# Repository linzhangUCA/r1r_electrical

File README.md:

# homer_ee
Electrical and electronics design for HomeR

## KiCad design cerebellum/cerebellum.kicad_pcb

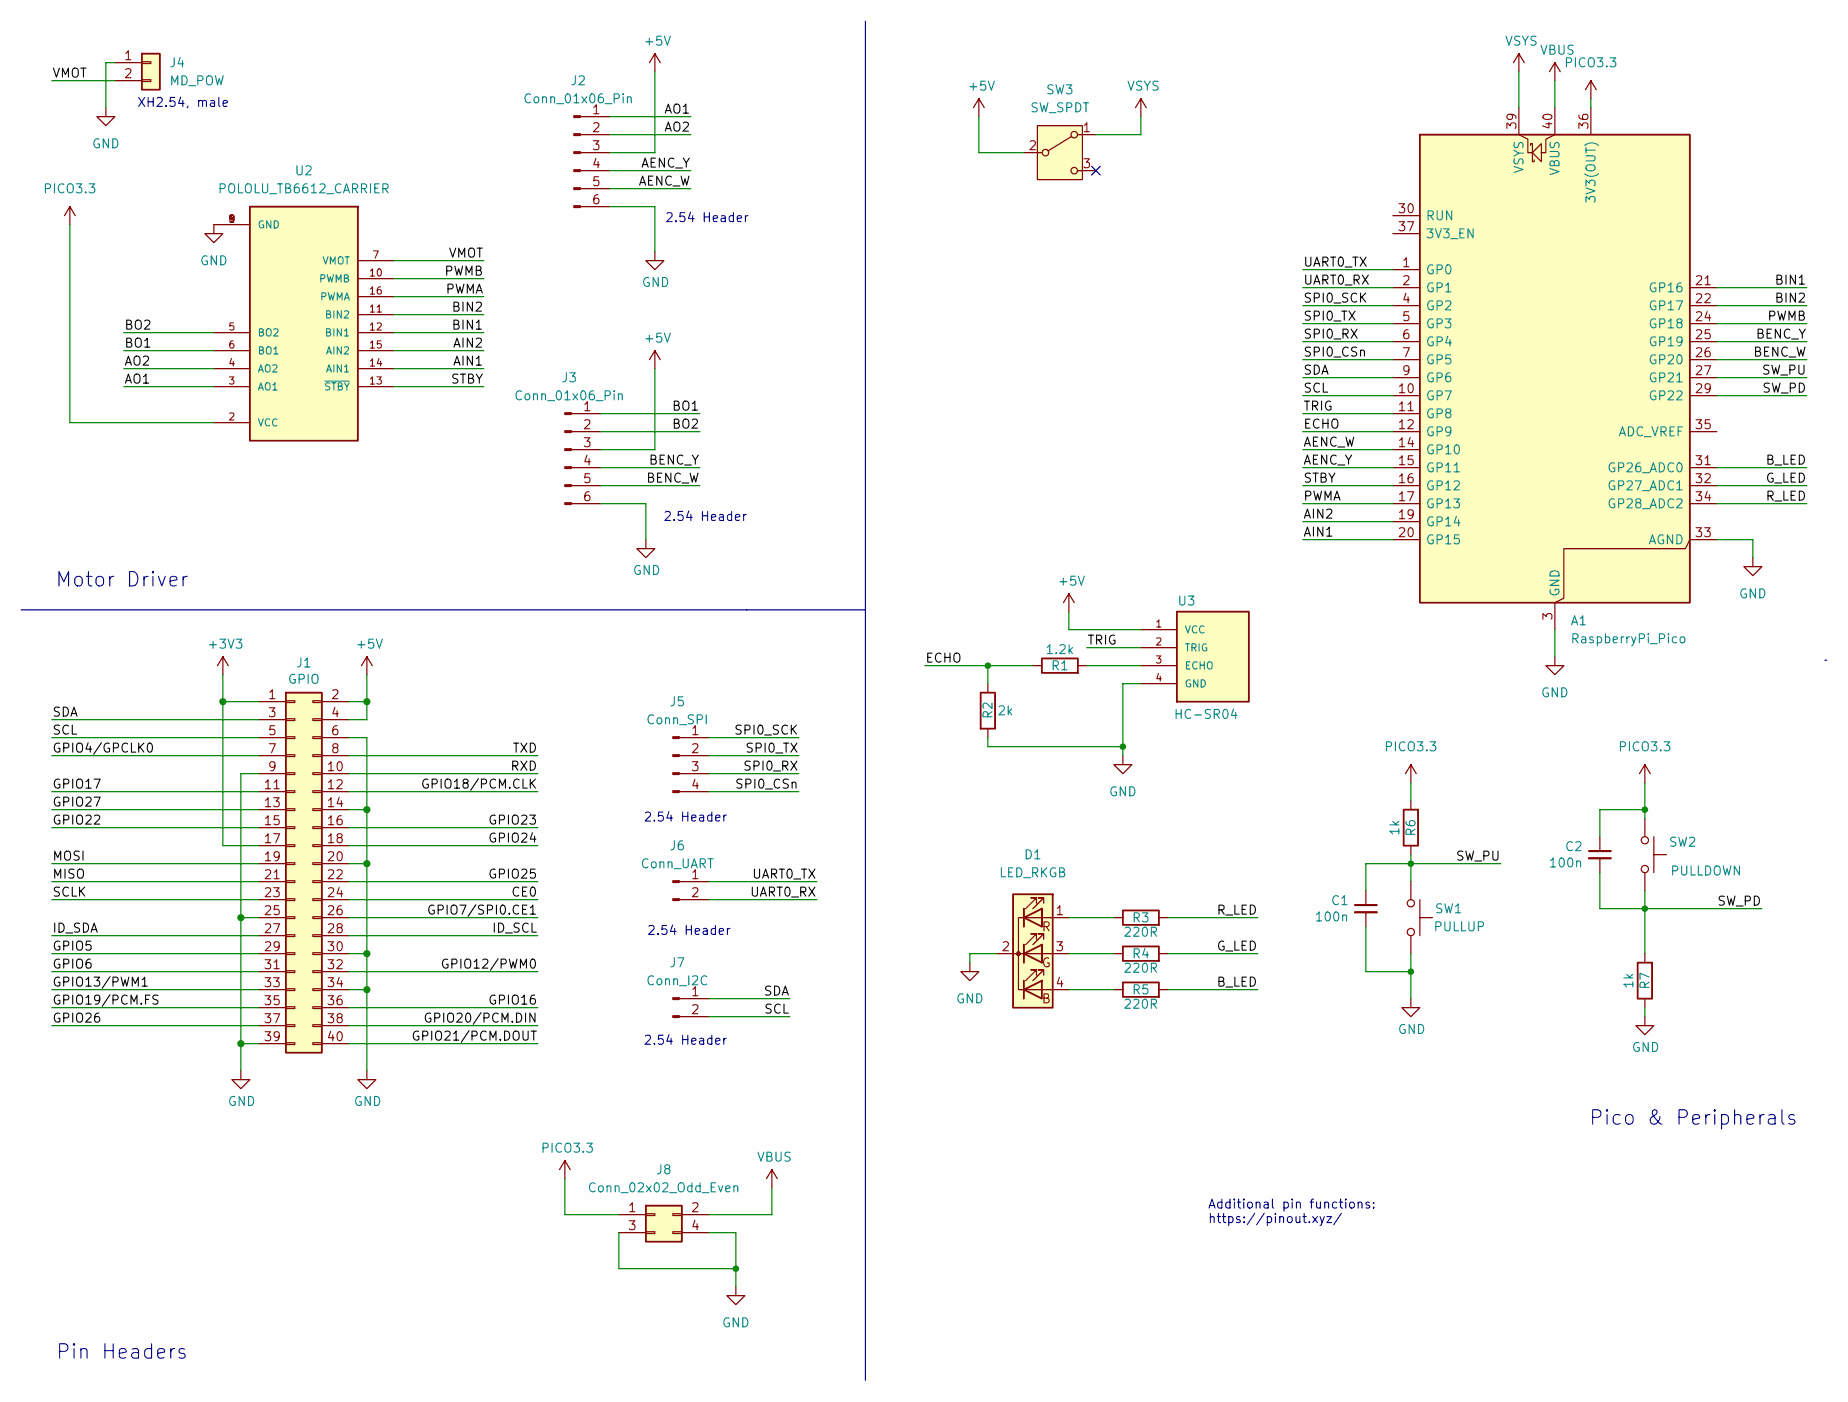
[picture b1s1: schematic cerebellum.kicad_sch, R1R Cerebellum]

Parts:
A1: RaspberryPi_Pico; RaspberryPi_Pico_Common_THT
C1, C2: 100n; C_Disc_D4.7mm_W2.5mm_P5.00mm
D1: LED_RKGB; LED_D5.0mm-4_RGB_Wide_Pins
J1: GPIO; PinSocket_2x20_P2.54mm_Vertical
J2, J3: Conn_01x06_Pin; PinHeader_1x06_P2.54mm_Vertical
J4: MD_POW; PinHeader_1x02_P2.54mm_Horizontal
J5: Conn_SPI; PinHeader_1x04_P2.54mm_Vertical
J6: Conn_UART; PinHeader_1x02_P2.54mm_Vertical
J7: Conn_I2C; PinHeader_1x02_P2.54mm_Vertical
J8: Conn_02x02_Odd_Even; PinHeader_2x02_P2.54mm_Vertical
R1: 1.2k; R_Axial_DIN0207_L6.3mm_D2.5mm_P10.16mm_Horizontal
R2: 2k; R_Axial_DIN0207_L6.3mm_D2.5mm_P10.16mm_Horizontal
R3, R4, R5: 220R; R_Axial_DIN0207_L6.3mm_D2.5mm_P10.16mm_Horizontal
R6, R7: 1k; R_Axial_DIN0207_L6.3mm_D2.5mm_P10.16mm_Horizontal
SW1: PULLUP; SW_PUSH_6mm_H5mm
SW2: PULLDOWN; SW_PUSH_6mm_H5mm
SW3: SW_SPDT; PinHeader_1x03_P2.54mm_Vertical
U2: POLOLU_TB6612_CARRIER; POLOLU_TB6612
U3: HC-SR04; XCVR_HC-SR04

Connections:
+3V3: J1.1, J1.17
+5V: J1.2, J1.4, J2.3, J3.3, SW3.2 (B), U3.1 (VCC)
/AENC_W: A1.14 (GP10), J2.5
/AENC_Y: A1.15 (GP11), J2.4
/AIN1: A1.20 (GP15), U2.14 (AIN1)
/AIN2: A1.19 (GP14), U2.15 (AIN2)
/AO1: J2.1, U2.3 (AO1)
/AO2: J2.2, U2.4 (AO2)
/BENC_W: A1.26 (GP20), J3.5
/BENC_Y: A1.25 (GP19), J3.4
/BIN1: A1.21 (GP16), U2.12 (BIN1)
/BIN2: A1.22 (GP17), U2.11 (BIN2)
/BO1: J3.1, U2.6 (BO1)
/BO2: J3.2, U2.5 (BO2)
/B_LED: A1.31 (GP26_ADC0), R5.2
/CE0: J1.24
/ECHO: A1.12 (GP9), R1.1, R2.1
/GPIO4/GPCLK0: J1.7
/GPIO5: J1.29
/GPIO6: J1.31
/GPIO7/SPI0.CE1: J1.26
/GPIO12/PWM0: J1.32
/GPIO13/PWM1: J1.33
/GPIO16: J1.36
/GPIO17: J1.11
/GPIO18/PCM.CLK: J1.12
/GPIO19/PCM.FS: J1.35
/GPIO20/PCM.DIN: J1.38
/GPIO21/PCM.DOUT: J1.40
/GPIO22: J1.15
/GPIO23: J1.16
/GPIO24: J1.18
/GPIO25: J1.22
/GPIO26: J1.37
/GPIO27: J1.13
/G_LED: A1.32 (GP27_ADC1), R4.2
/ID_SCL: J1.28
/ID_SDA: J1.27
/MISO: J1.21
/MOSI: J1.19
/PWMA: A1.17 (GP13), U2.16 (PWMA)
/PWMB: A1.24 (GP18), U2.10 (PWMB)
/RXD: J1.10
/R_LED: A1.34 (GP28_ADC2), R3.2
/SCL: A1.10 (GP7), J1.5, J7.2
/SCLK: J1.23
/SDA: A1.9 (GP6), J1.3, J7.1
/SPI0_CSn: A1.7 (GP5), J5.4
/SPI0_RX: A1.6 (GP4), J5.3
/SPI0_SCK: A1.4 (GP2), J5.1
/SPI0_TX: A1.5 (GP3), J5.2
/STBY: A1.16 (GP12), U2.13 (~STBY)
/SW_PD: A1.29 (GP22), C2.2, R7.2, SW2.2
/SW_PU: A1.27 (GP21), C1.1, R6.1, SW1.1
/TRIG: A1.11 (GP8), U3.2 (TRIG)
/TXD: J1.8
/UART0_RX: A1.2 (GP1), J6.2
/UART0_TX: A1.1 (GP0), J6.1
/VMOT: J4.2, U2.7 (VMOT)
GND: A1.3 (GND), A1.8 (GND), A1.13 (GND), A1.18 (GND), A1.23 (GND), A1.28 (GND), A1.33 (AGND), A1.38 (GND), C1.2, D1.2 (K), J1.6, J1.9, J1.14, J1.20, J1.25, J1.30, J1.34, J1.39, J2.6, J3.6, J4.1, J8.3, J8.4, R2.2, R7.1, SW1.2, U2.1 (GND), U2.8 (GND), U2.9 (GND), U3.4 (GND)
unnamed: D1.4 (BA), R5.1
unnamed: D1.3 (GA), R4.1
unnamed: D1.1 (RA), R3.1
unnamed: R1.2, U3.3 (ECHO)
PICO3.3: A1.36 (3V3(OUT)), C2.1, J8.1, R6.2, SW2.1, U2.2 (VCC)
VBUS: A1.40 (VBUS), J8.2
VSYS: A1.39 (VSYS), SW3.1 (A)

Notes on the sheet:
2.54 Header
Pin Headers
Additional pin functions: https://pinout.xyz/
Pico & Peripherals
Motor Driver
XH2.54, male

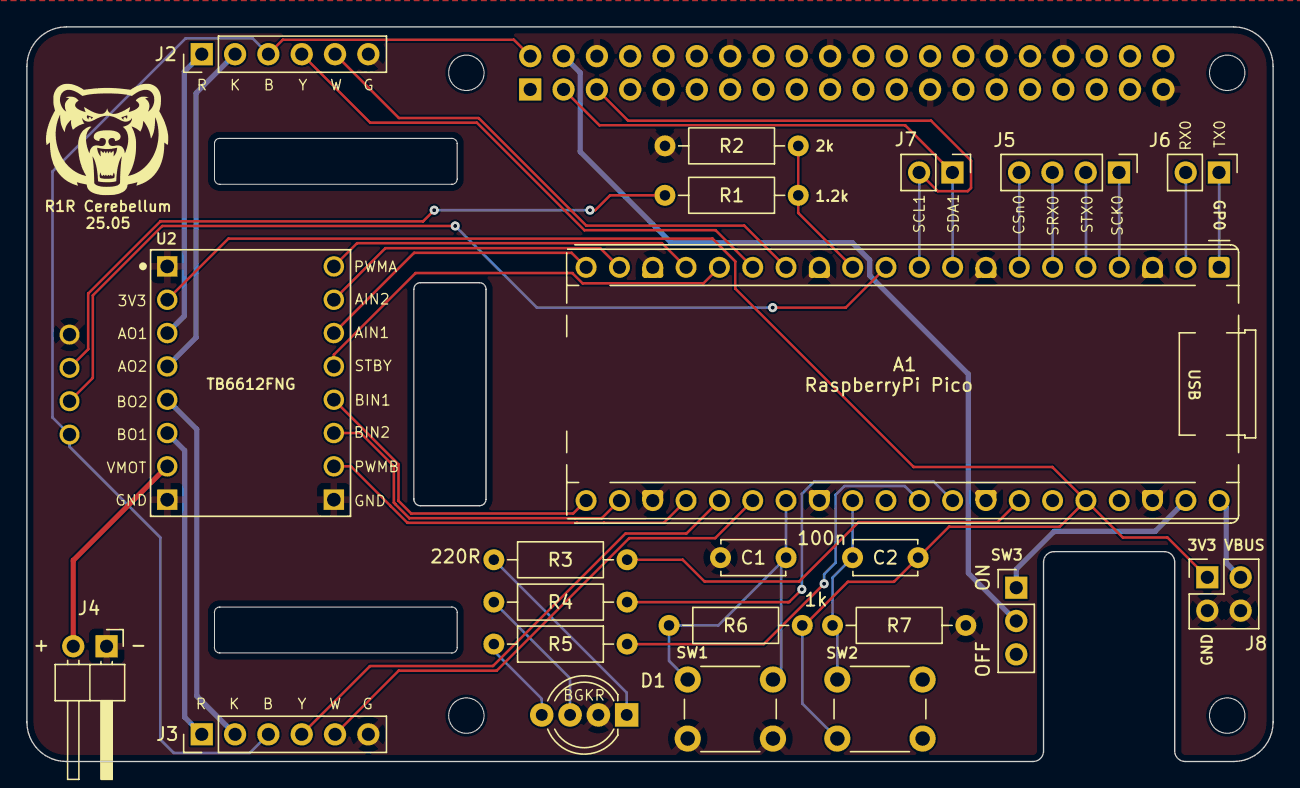
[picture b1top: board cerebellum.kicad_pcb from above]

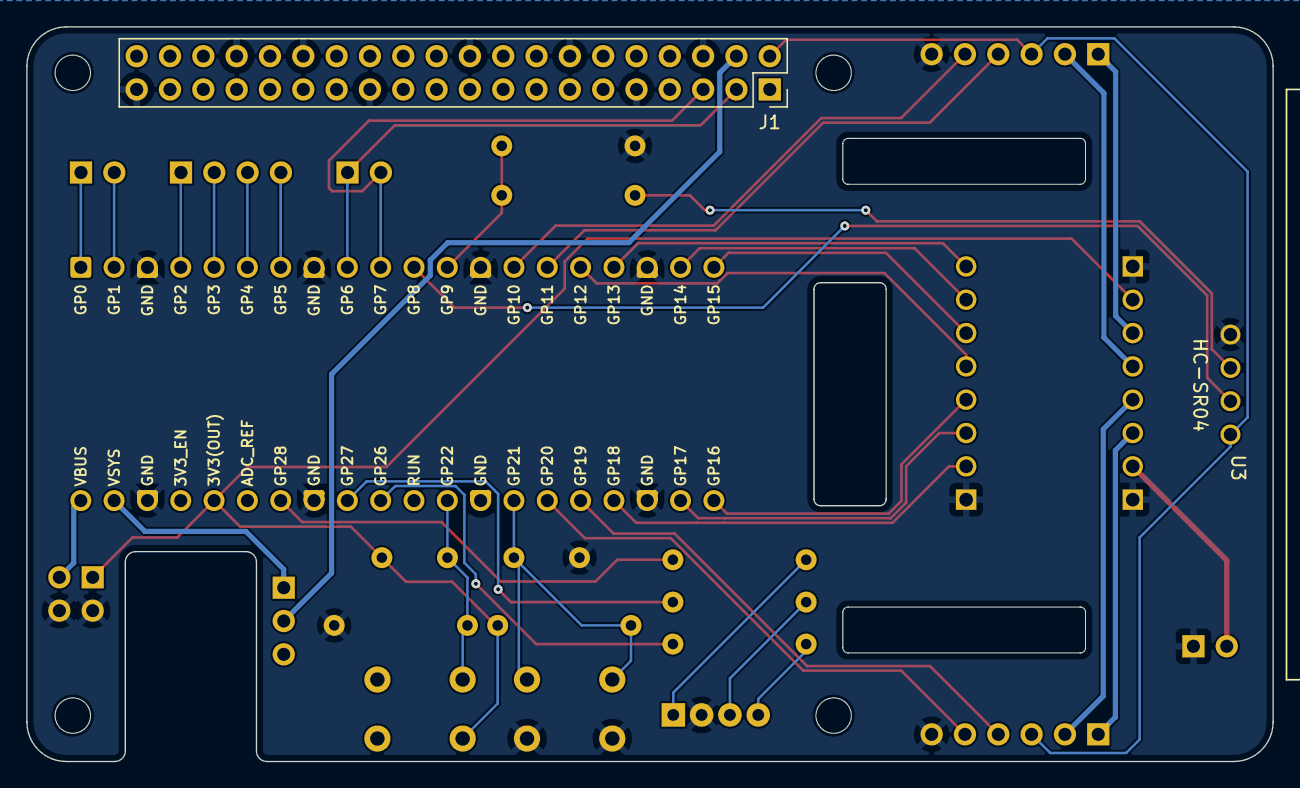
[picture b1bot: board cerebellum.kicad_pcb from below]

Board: 4 copper layers, 95.0 x 56.0 mm, 28 parts (2 on the bottom side), 41 nets.

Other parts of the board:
MH1, MH2, MH3, MH4: MountingHole_2.7mm_M2.5

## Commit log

2025-04-17 init homer cerebellum project
2025-04-17 add lib for pololu tb6612
2025-04-17 update local libs
2025-04-17 update design
2025-04-17 label comm pins
2025-04-18 update schematic
    assign labels to pico
2025-04-18 update schematic
    added HC-SR04
2025-04-18 update schematic
    added RGB LED
2025-04-18 update schematic
    added pull-up and pull-down switches
2025-04-18 update schematic
    added spdt switch to power pico
2025-04-18 update schematic
    added motor connectors
2025-04-18 update schematic
    updated scheme info
2025-04-18 update schematic
    added uart and spi conns
2025-04-18 update design
    added instructions for connectors
2025-04-18 update schematic
    add VBUS and I2C header pins
2025-04-18 update date
2025-04-18 update schematic and pcb
    assigned footprints
2025-04-19 update pico footprint
2025-04-19 update pcb
2025-04-19 update pcb
    cut camera slot
2025-04-19 update pcb
    enlarge board
2025-04-19 update md wiring
    split motor a and b to two sides
2025-04-23 update schematic
    debounce switches
2025-04-23 update pcb
    use pcbway template
2025-04-23 update design
    wire up
2025-04-24 update pcb
    add labels
2025-04-24 generate gerbers
2025-04-24 save pcb
2025-04-25 remove eeprom from schematic
2025-04-25 update footprints
2025-04-26 adjust layout
2025-04-26 update layout
2025-04-27 update wiring
2025-05-21 organize schematic
2025-05-21 update motor connector in schematic
2025-05-21 update symbol and footprint
2025-05-21 update resistors and capacitors footprint to tht
2025-05-21 update pcb layout
2025-05-21 update pcb wiring
2025-05-21 export pcb step
2025-05-22 drill two rectangle holes on pcb for motor wiring
2025-05-22 update pico power outlet pins footprint
2025-05-22 export updated pcb model
2025-05-22 save schematic change, minor
2025-05-23 fix pcb
2025-05-23 export fixed pcb
2025-05-24 generate new gerbers for pcbway
2025-05-24 save project
2025-05-24 generate gerbers for jlcpcb
2025-05-24 remove old gerbers
